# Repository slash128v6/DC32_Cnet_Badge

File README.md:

# DC32 CompuNet Badge 
## Description
The **Fony Bitman** by CompuNet is a cutting-edge, compact, and highly versatile device designed to seamlessly integrate with modern lifestyles. This device harnesses the robust capabilities of the ESP32 microcontroller, known for its high performance, low power consumption, and advanced wireless connectivity features.

*Key Features:*

Arduino-based ESP32 Microcontroller: At its core, the **Fony Bitman** features Wi-Fi and Bluetooth connectivity, as well as high-fidelity mono sound with redundant output (a second speaker).

Customizable and Expandable: The **Fony Bitman** by CompuNet is highly customizable, allowing developers to create tailored applications and features. Its expandable nature supports various sensors and modules, enhancing functionality for specific use cases. If you don't like how it works, re-engineer accordingly.

This device is not UL listed, certified, warranteed or recommended for anyone that is adverse to sharp, dangerous objects. As with all electronics projects, unplug when not in use and store safely to avoid fires, spontanious combustion, itching or burning sensations. 

Do not taunt the **Fony Bitman**.

## Badge Operation

The power switch selects battery power or USB power. USB power will charge the battery. The battery must be sufficiently charged for battery operation. If the badge does not operate on battery power let it charge via USB. There is a battery “gas gauge” on the charge module that is viewable from the front of the board.

From your phone connect to Bluetooth device “FONY BITMAN”. Sound should play through the speakers and the LED strips should react to the music. The touch pads on the top front of the badge should act as music and volume controls.

## Part 1: Badge Assembly

### Badge Parts List

| QTY | Description        |
|-----|--------------------|
| 1   | 2 pos CONN HEADER  |
| 1   | switch             |
| 1   | 6 pos CONN HEADER  |
| 1   | 16 pos CONN HEADER |
| 1   | ESP-32             |
| 2   | LED Stick          |
| 1   | Amp                |
| 2   | speaker            |
| 1   | charge module      |
| 3   | foam tape          |
| 1   | battery            |

### Step 1: Front view:

### Step 2: Rear View

### Step 3: Solder LED strips to front

The DI (Data In) side connects to the badge pads.

### Step 4: Tin the LED & badge pads

### Step 5: Apply first LED

Line up the LED strip pads on the badge pads leaving the ends of the badge pads exposed so you can heat them up with your soldering iron. It’s a little tricky but you should be able to get the solder to flow and insert some solder from the sides of the pads to connect the pads. Try to keep the LED strip straight. 

### Step 6: Repeat for the second LED strip

### Step 7: Power Switch

Solder the power switch on the back with the switch tab facing up

### Step 8: Solder the SAO connector

Solder the SAO connector with the tab up matching the outline keeping it straight and parallel to the bottom oedge of the badge

### Step 9: Battery Charger Module

Locate the battery charger module and pin header and cut off 6 pins

### Step 10: Solder the module header

Solder the 6 pin header to the charge module with the short pins protruding through the white silkscreen side of the charge module

### Step 11: Attach module to the badge

Solder the charge module to the back of the badge

### Step 12: Verify LED visibility

The charge module battery level LEDs should be visibile through the front of the badge

### Step 13: Amplifier module

Locate the amplifier module and pin header, the green screw terminal is not needed and can be discarded

### Step 14: Solder amp header

Solder the pin header to the amplifier with the short side of the pins protruding through the silkscreen pin label side of the amplifier module

### Step 15: Attach pins to speaker outs

15)	Cut 2 more single pins and solder them to the speaker outputs with the short side protruding through the silkscreen pin label side of the amplifier module

### Step 16: Attach amp module to badge

Solder the amplifier module through the back of the badge

### Step 17: ESP32 Module

Solder the ESP32 module to the back of the badge with the USB connector oriented to the silkscreen outline which should face the CompuNet logo

### Step 18: Battery Connector

Solder the battery connector to the back of the badge

### Step 19: Speaker Wire

Trim the speaker wires leaving a few inches and run the speaker wires through the holes as shown for strain relief 

### Step 20: Tape Speakers

Cut two pieces of double-sided foam for speaker mounting (leave enough for a third piece for battery mounting)

### Step 21: Attach Speakers

Mount the speakers to the badge using the foam tape by standing the badge and speakers upraight before pressing them together so it balances and doesn’t tip over

### Step 22: Speaker Wires

Split and trim the speaker wires to solder to the badge

### Step 23: Solder Speaker Wires

Solder the speaker wires to the badge noting polarity – red to (+) and black to (-)

### Step 24: Power pigtail

Locate the JST PH 1.25 and JST PH 2.0 pigtail leads and 1 piece of heat shrink

### Step 25: Polarity Check

_***Important!***_

Verify Polarity!

Due to a part change with the JST PH 2.0 pigtail please confirm that the wires are in the correct position matching the photo above. If they are opposite then you need to swap them around by carefully lifting up the plastic tabs with tweezers, removing each wire, then slide them back in to the opposite side. 

**ASK IF YOU NEED HELP WITH THIS. PERFORMING THIS STEP INCORRECTLY WILL DAMAGE YOUR BADGE AND COULD BE A FIRE HAZZARD. 

PROCEED WITH CAUTION!!**

### Step 26: Pigtail

Slip the 2 pieces of heat shrink onto the JST PH 2.0 pig tail (fatter wires), then strip and tin the ends

### Step 27: Solder the Cables

Solder the wires together RED to RED and BLACK to BLACK, a set of “helping hands” can be helpful 😊

### Step 28: Apply Heatshrink

### Step 29: Badge Adhesive

Place the last piece if the double sided tape in the battery location on the back of the badge

### Step 30: Battery Leads

Route the battery leads using the pigtail connector, the leads can be tucked under the edges of the battery.

**Verify polarity is correct before connecting. If you're not sure, please ask.**

## Part 2: Badge Programming

Check out the badge programming doc [here](https://github.com/slash128v6/DC32_Cnet_Badge/blob/main/Docs/programming.md)

## Part 3: SAO Builds

Check out the SAO build doc [here](https://github.com/slash128v6/DC32_Cnet_Badge/blob/main/Docs/sao.md)

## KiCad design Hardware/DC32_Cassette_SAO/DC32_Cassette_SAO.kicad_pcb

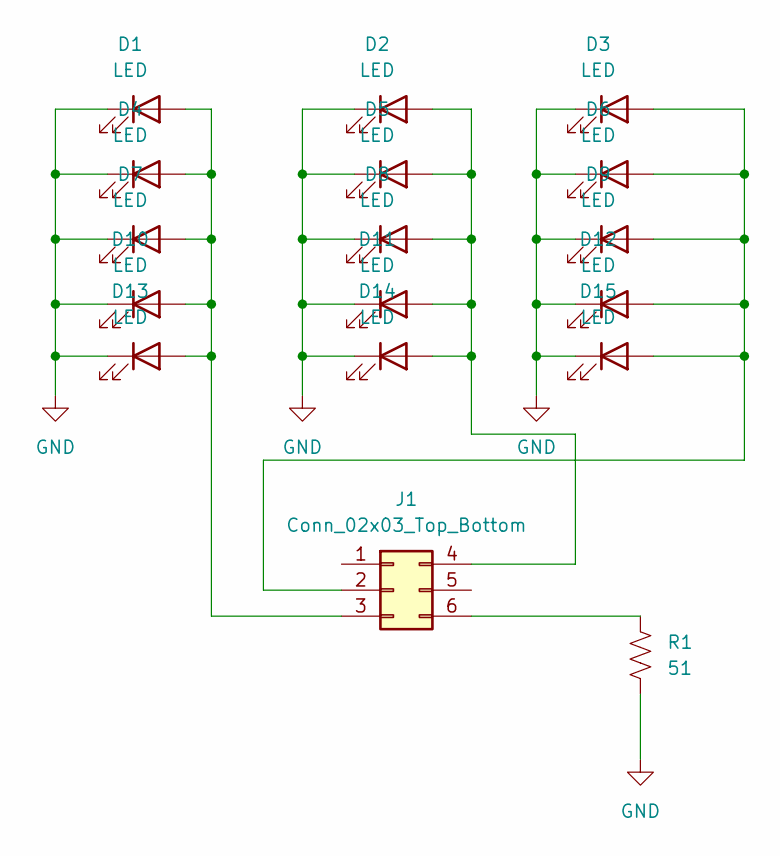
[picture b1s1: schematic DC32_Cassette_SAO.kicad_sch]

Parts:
D1, D2, D3, D4, D5, D6, D7, D8, D9, D10, D11, D12, D13, D14, D15: LED; LED_D3.0mm
J1: Conn_02x03_Top_Bottom; PinSocket_2x03_P2.54mm_Vertical_Tab
R1: 51; R_Axial_DIN0207_L6.3mm_D2.5mm_P7.62mm_Horizontal

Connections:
GND: D1.1 (K), D2.1 (K), D3.1 (K), D4.1 (K), D5.1 (K), D6.1 (K), D7.1 (K), D8.1 (K), D9.1 (K), D10.1 (K), D11.1 (K), D12.1 (K), D13.1 (K), D14.1 (K), D15.1 (K), R1.2
unnamed: D1.2 (A), D4.2 (A), D7.2 (A), D10.2 (A), D13.2 (A), J1.3
unnamed: D2.2 (A), D5.2 (A), D8.2 (A), D11.2 (A), D14.2 (A), J1.4
unnamed: D3.2 (A), D6.2 (A), D9.2 (A), D12.2 (A), D15.2 (A), J1.2
unnamed: J1.6, R1.1

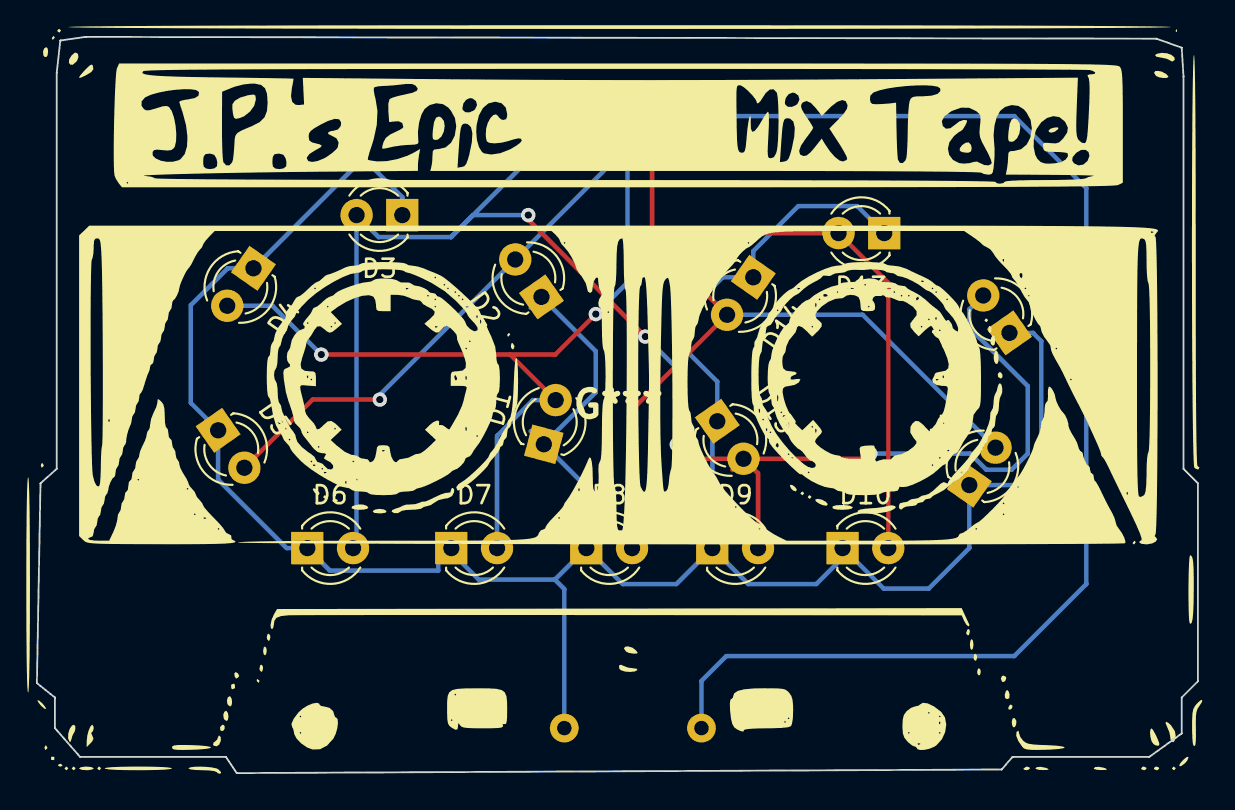
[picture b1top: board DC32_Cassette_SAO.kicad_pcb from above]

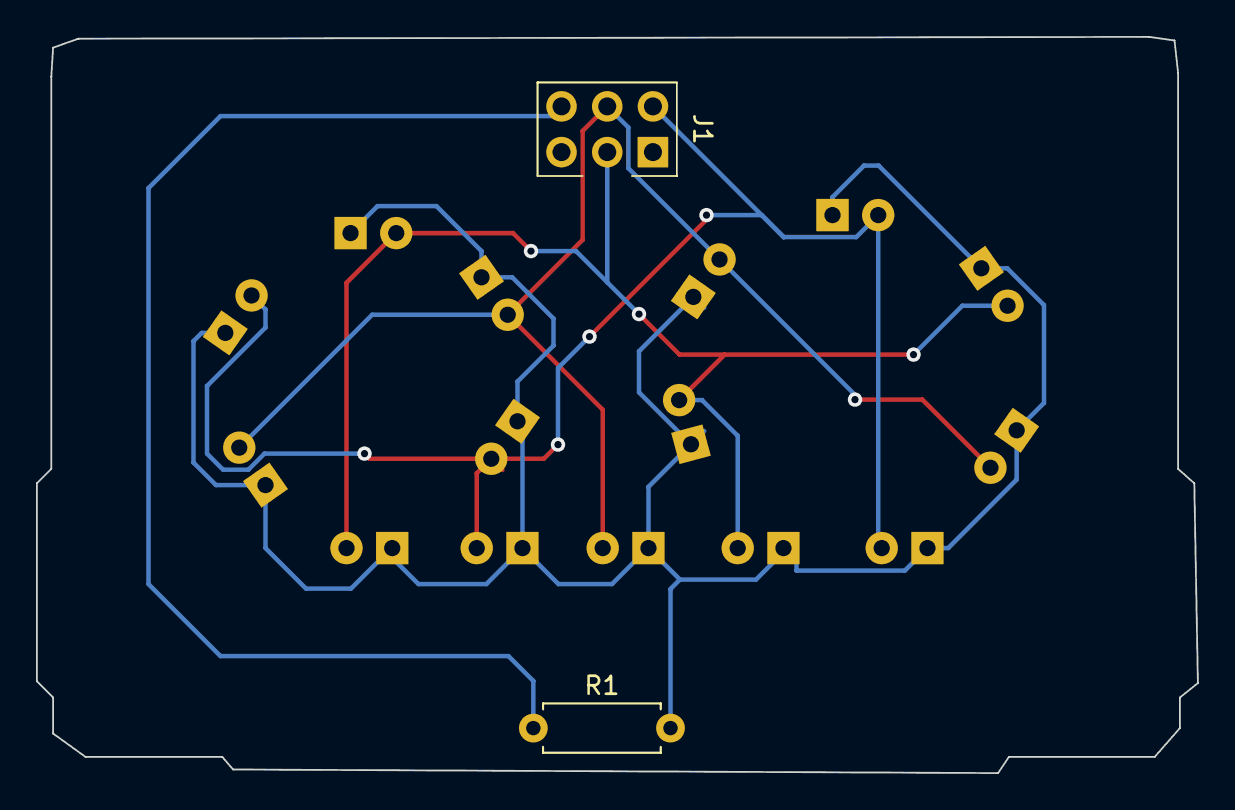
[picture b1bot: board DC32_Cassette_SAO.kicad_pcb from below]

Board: 2 copper layers, 64.5 x 40.9 mm, 17 parts (2 on the bottom side), 5 nets.

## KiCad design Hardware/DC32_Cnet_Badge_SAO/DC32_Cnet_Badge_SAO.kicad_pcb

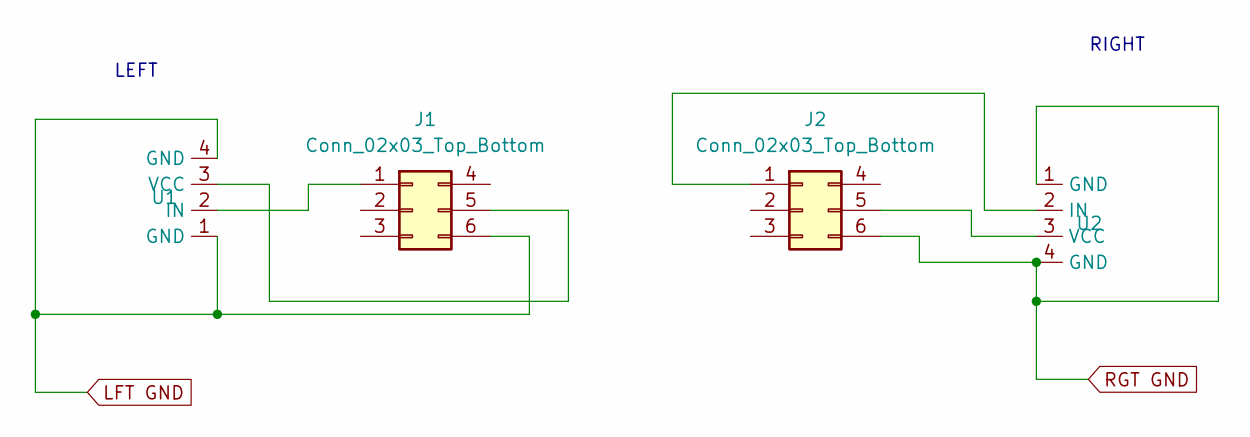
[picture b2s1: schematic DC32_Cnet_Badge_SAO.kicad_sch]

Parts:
J1, J2: Conn_02x03_Top_Bottom; PinSocket_2x03_P2.54mm_Vertical_Tab
U1, U2: LED_SAO

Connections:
LFT GND: J1.6, U1.1 (GND), U1.4 (GND)
unnamed: J1.1, U1.2 (IN)
unnamed: J1.5, U1.3 (VCC)
unnamed: J2.1, U2.2 (IN)
unnamed: J2.5, U2.3 (VCC)
RGT GND: J2.6, U2.1 (GND), U2.4 (GND)

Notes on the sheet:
LEFT
RIGHT

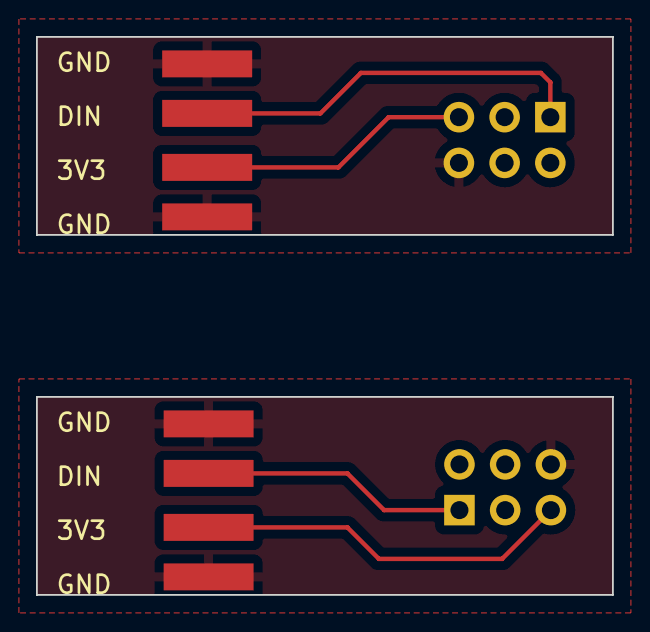
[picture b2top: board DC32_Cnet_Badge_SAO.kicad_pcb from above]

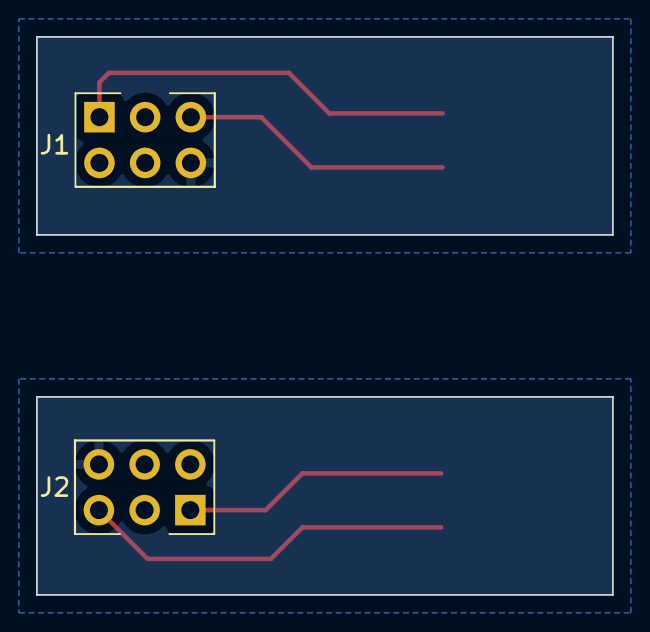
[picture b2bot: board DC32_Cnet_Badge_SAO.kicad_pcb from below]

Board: 2 copper layers, 32.0 x 31.0 mm, 4 parts (2 on the bottom side), 6 nets.

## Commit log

2024-02-19 Software Restructure
2024-02-19 Software push
2024-02-19 Incremental Commit
2024-02-29 Added touch debounce
2024-03-01 Reverted to ESP32 2.0.12
    ESP32 2.0.14 has issues with Bluetooth signal quality.
2024-03-07 Incremental
2024-03-11 PCB updates
2024-03-18 New PCB Designs
2024-05-24 Docs
2024-05-26 Updated docs
2024-05-30 Docs updated
2024-06-10 Updated ReadMe with new battery connectors
2024-07-24 Updated schematics and generated PDFs
2024-08-02 modified: README.md
2024-08-02 docs update
2024-08-02 doc update
2024-08-05 Reduced "touchThresholds" to reduce sporadic touch events
2024-08-06 added parts list
2024-08-06 readme update
2024-08-06 added programming.md
2024-08-10 sao added
2024-08-10 README updated
2024-09-09 Organized
